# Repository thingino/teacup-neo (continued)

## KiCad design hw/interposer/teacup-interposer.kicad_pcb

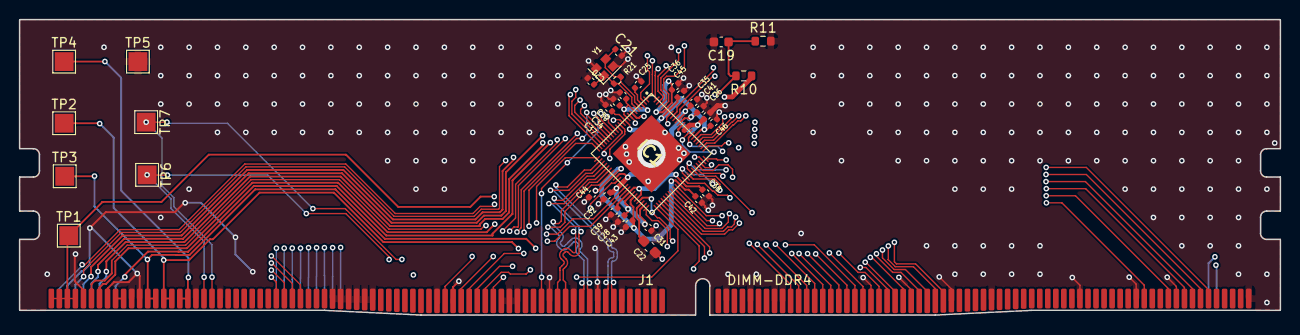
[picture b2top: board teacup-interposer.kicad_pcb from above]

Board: 4 copper layers, 133.3 x 31.2 mm, 35 parts (0 on the bottom side), 72 nets.

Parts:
C19: 100nF; C_0603_1608Metric
C20, C21: 12pF; C_0402_1005Metric
C22: 4.7uF; C_0603_1608Metric_Pad1.08x0.95mm_HandSolder
C25, C26, C28, C30, C31, C32, C34, C35, C36, C37, C38, C39, C41, C42, C43, C44, C45, C46: 100nF; C_0402_1005Metric
IC1: T31ZX; QFN35P900X900X90-89N-D
J1: DIMM-DDR4
R10, R11: 100k; R_0603_1608Metric
R21: 1M; R_0402_1005Metric
TP1: VCORE; TestPoint_Pad_2.0x2.0mm
TP2: +1V8; TestPoint_Pad_2.0x2.0mm
TP3: +3V3; TestPoint_Pad_2.0x2.0mm
TP4: +5V_SW; TestPoint_Pad_2.0x2.0mm
TP5: GND; TestPoint_Pad_2.0x2.0mm
TP6: USBA_HOST_DP; TestPoint_Pad_2.0x2.0mm
TP7: USBA_HOST_DM; TestPoint_Pad_2.0x2.0mm
Y1: 24 MHz; Crystal_SMD_2016-4Pin_2.0x1.6mm

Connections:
+1V8: C25.1, C26.1, C28.1, C30.1, C31.1, C32.1, C34.1, C35.1, IC1.3 (VDDIO_OSC), IC1.6 (PLL_VDDHV), IC1.9 (VDDIO0), IC1.31 (MIPI_AVD18), IC1.33 (ADC_VREF), IC1.34 (ADC_AVDD), IC1.38 (USB_AVD18), IC1.43 (CODEC_AVDD), IC1.75 (DDRVDD), IC1.76 (VDDMEM), IC1.79 (DDRPLL_VCCA), J1.15, J1.16, R10.1, TP2.1 (1_1)
+3V3: C36.1, C38.1, C39.1, IC1.37 (USB_AVD33), IC1.40 (VDDIO2), IC1.56 (VDDIO1_1), IC1.84 (VDDIO1_2), J1.13, J1.14, TP3.1 (1_1)
+5V_SW: J1.17, J1.18, TP4.1 (1_1)
/EXCLK_I: C20.1, IC1.5 (EXCLK_I), R21.1, Y1.1
/EXCLK_O: C21.1, IC1.4 (EXCLK_O), R21.2, Y1.3
/VCM: C22.1, IC1.42 (VCM)
/VREF: C19.1, IC1.77 (VREF), R10.2, R11.1
GMAC0_MDCK: IC1.58 (GMAC_MDCK_MSC1_D0_I2S_SDTO_SLCD_D4_PB10), J1.88
GMAC0_MDIO: IC1.57 (GMAC_MDIO_MSC1_D1_SLCD_D5_PB11), J1.87
GMAC0_PHYCLK: IC1.63 (GMAC_PHY_CLK_SLCD_D1_PB07), J1.90
GMAC0_RXD0: IC1.60 (GMAC_RXD0_I2S_DAC_LRCK_SLCD_WR_PB15/_SF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), J1.95
GMAC0_RXD1: IC1.61 (GMAC_RXD1_SLCD_TE_PB16/_SFC_GPC_PA25), J1.96
GMAC0_RXDV: IC1.59 (GMAC_RXDV_MSC1_CMD_I2S_SDTI_SLCD_D3_PB09), J1.94
GMAC0_TXCLK: IC1.62 (GMAC_TXCLK_SLCD_D0_PB06), J1.89
GMAC0_TXD0: IC1.64 (GMAC_TXD0_MSC1_D2_I2S_ADC_LRCK_SLCD_D6_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), J1.92
GMAC0_TXD1: IC1.65 (GMAC_TXD1_MSC1_D3_I2S_DAC_MCLK_SLCD_D7_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), J1.93
GMAC0_TXEN: IC1.66 (GMAC_TXEN_MSC1_CLK_I2S_ADC_MCLK_SLCD_D2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), J1.91
GND: C19.2, C20.2, C21.2, C22.2, C25.2, C26.2, C28.2, C30.2, C31.2, C32.2, C34.2, C35.2, C36.2, C37.2, C38.2, C39.2, C41.2, C42.2, C43.2, C44.2, C45.2, C46.2, IC1.89 (EP), J1.5, J1.8, J1.11, J1.12, J1.19, J1.22, J1.36, J1.37, J1.38, J1.39, J1.40, J1.41, J1.49, J1.51, J1.57, J1.58, J1.59, J1.63, J1.66, J1.69, J1.72, J1.76, J1.79, J1.82, J1.85, J1.86, J1.97, J1.102, J1.107, J1.112, J1.123, J1.130, J1.135, J1.144, J1.145, J1.147, J1.152, J1.169, J1.170, J1.171, J1.172, R11.2, TP5.1 (1_1), Y1.2 (G), Y1.4 (G)
GPIO0: IC1.80 (GPIO_PB31), J1.153
HPOUTL: IC1.44 (HPOUTL), J1.7
MICLP: IC1.41 (MICLP), J1.6
MIPI0_CLKN: IC1.26 (MIPI_CLKN_DVP_D3), J1.65
MIPI0_CLKP: IC1.27 (MIPI_CLKP_DVP_D2), J1.64
MIPI0_D0N: IC1.24 (MIPI_DATAN0_DVP_D5), J1.71
MIPI0_D0P: IC1.25 (MIPI_DATAP0_DVP_D4), J1.70
MIPI0_D1N: IC1.28 (MIPI_DATAN1_DVP_D1), J1.68
MIPI0_D1P: IC1.29 (MIPI_DATAP1_DVP_D0), J1.67
MIPI0_GPIO: IC1.16 (SA1_DVP_MCLK_PA15), J1.62
MSC0_CLK: IC1.51 (MSC0_CLK_SSI_SLV_CLK_PB04), J1.53
MSC0_CMD: IC1.52 (MSC0_CMD_SSI_SLV_CE0_PB05), J1.54
MSC0_D0: IC1.50 (MSC0_D0_SSI_SLV_DT_PB00), J1.52
MSC0_D1: IC1.49 (MSC0_D1_SSI_SLV_DR_PB01), J1.50
MSC0_D2: IC1.54 (MSC0_D2_PB02), J1.56
MSC0_D3_CD: IC1.53 (MSC0_D3_PB03), J1.55
MSC1_CLK: IC1.15 (CS2_DVP_HSYNC_SMB1_SDA_MSC1_CLK_PA16), J1.283
MSC1_CMD: IC1.14 (RD_DVP_VSYNC_SMB1_SCK_MSC1_CMD_PA17), J1.284
PWM0: IC1.1 (PWM0_SSI1_DT_PB17), J1.136
PWM1: IC1.2 (PWM1_SSI1_DR_PB18), J1.137
PWM2: IC1.86 (PWM2_SSI1_DT_DRV_VBUS_PB27), J1.138
PWM3: IC1.85 (PWM3_SSI1_DR_DMIC_CLK_PB28), J1.139
SAR_AUX0: IC1.32 (ADC_AUX0), J1.146
SFC_CLK: IC1.48 (SFC_CLK_PA27), J1.30
SFC_CS: IC1.45 (SFC_CE0_PA28), J1.32
SFC_IO0: IC1.47 (SFC_DT_PA23), J1.31
SFC_IO1: IC1.46 (SFC_DR_PA24), J1.29
SMB0_SCK: IC1.12 (SD7_SMB0_SCK_PA13), J1.149
SMB0_SDA: IC1.13 (SD6_SMB0_SDA_PA12), J1.148
SMB1_SCK: IC1.87 (SMB1_SCK_SSI1_CLK_PB26), J1.151
SMB1_SDA: IC1.88 (SMB1_SDA_SSI1_CE0_PB25), J1.150
SPARE_P173: IC1.7 (PPRST_), J1.173
SPARE_P174: IC1.8 (EFUSE_AVD), J1.174
SPARE_P175: IC1.11 (SA2_PA18), J1.175
SPARE_P176: IC1.17 (SA0_DVP_PCLK_PWM0_PA14), J1.176
SPARE_P177: IC1.22 (SD1_DVP_D7_UART1_RXD_PA07), J1.177
SPARE_P178: IC1.23 (SD0_DVP6_UART1_TXD_PA06), J1.178
SPARE_P179: IC1.67 (BOOT_SEL0_PC00), J1.179
SPARE_P180: IC1.73 (UART1_RXD_TMS_PB24), J1.180
SPARE_P181: IC1.74 (UART1_TXD_TCK_PB23), J1.181
SSI1_CE0: IC1.81 (SSI1_CE0_DMIC_DAT1_PB30), J1.134
SSI1_CLK: IC1.82 (SSI1_CLK_DMIC_DAT0_PB29), J1.131
UART0_CTS: IC1.69 (UART0_CTS_I2S_ADC_BCLK_SLCD_CS_PB20), J1.100
UART0_RTS: IC1.68 (UART0_RTS_I2S_DAC_BCLK_SLCD_DC_PB21), J1.101
UART0_RXD: IC1.71 (UART0_RXD_TDI_PB19), J1.98
UART0_TXD: IC1.70 (UART0_TXD_TDO_SLCD_RDY_PB22), J1.99
UART2_CTS: IC1.21 (SD2_DVP_D8_UART2_CTS_MSC1_D0_PA08), J1.105
UART2_RTS: IC1.20 (SD3_DVP_D9_UART2_RTS_MSC1_D1_PA09), J1.106
UART2_RXD: IC1.18 (SD5_DVP_D11_UART2_RXD_MSC1_D3_PA11), J1.103
UART2_TXD: IC1.19 (SD4_DVP_D10_UART2_TXD_MSC1_D2_PA10), J1.104
USBA_HOST_DM: IC1.35 (USB0PN), J1.21, TP7.1 (1_1)
USBA_HOST_DP: IC1.36 (USB0PP), J1.20, TP6.1 (1_1)
VCORE: C37.1, C41.1, C42.1, C43.1, C44.1, C45.1, C46.1, IC1.10 (VDD_1), IC1.30 (MIPI_AVD08), IC1.39 (VDD_2), IC1.55 (VDD_3), IC1.72 (VDD_4), IC1.78 (DDRPLL_VCCD), IC1.83 (VDD_5), J1.1, J1.2, J1.3, J1.4, TP1.1 (1_1)
VDDR: J1.9, J1.10

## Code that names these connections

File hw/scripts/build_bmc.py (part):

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    12: "BOOTSEL",
    13: "BMC_USB_DM", 14: "BMC_USB_DP",   # now via dedicated J9, not J2
    15: "RESET_EN",
    16: "SW5V_EN_ALT",               # GPIO select: alt-branch load switch (U14) -- native, margin testing
    17: "SFC_IO3", 18: "SFC_CS", 19: "SFC_IO0",
    20: "SFC_CLK", 21: "SFC_IO1", 22: "SFC_IO2",
    23: "HOSTED_SPI_MISO", 24: "HOSTED_SPI_CS",    # ESP-Hosted full-duplex SPI to interposer
    25: "HOSTED_HANDSHAKE",          # ESP-Hosted: co-processor -> host, data-ready-to-send
    26: "HOSTED_DATA_READY",         # ESP-Hosted: co-processor -> host, packet pending
    27: "U8_BOOT",                  # GPIO0/BOOT strap, R9 pull-up
    28: "EXP_INT",                   # U15 (TCA9555) interrupt, active low
    29: None, 35: None,              # spare
    30: "EN_CS_U4", 31: "EN_CS_U5",  # native, margin testing
    32: "USB_OC1", 33: "USB_OC2", 34: "USB_OC3",   # native -- fast overcurrent response
    36: "ESP32_CONSOLE_RX", 37: "ESP32_CONSOLE_TX",
    38: "SW5V_EN_BMC", 39: "VCORE_SNS",   # GPIO select: BMC-branch load switch (U4) -- native, margin testing
}
for num, spec in U8_PINS.items():
    ic_pin(U8, u8x, u8y, num, spec)
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    s.place(TS, ref, "TS5A3166", tx, y, 0, footprint="Package_TO_SOT_SMD:SOT-23-5",
            ref_at=(tx, y - S(6), 0), value_at=(tx, y + S(6), 0))
    ic_pin(TS, tx, y, 1, no_net)      # NO
    ic_pin(TS, tx, y, 2, "SFC_CS")    # COM
    ic_pin(TS, tx, y, 3, GNDF)        # GND
    ic_pin(TS, tx, y, 4, in_net)      # IN
    ic_pin(TS, tx, y, 5, P3V3F)       # V+
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s.place(SW, "SW1", "SSSS711403", swx, swy, 0,
        footprint="teacup-carrier:SW-TH_SSSS711403",
        ref_at=(swx, swy + S(4), 0), value_at=(swx, swy + S(6), 0))
ic_pin(SW, swx, swy, 1, "SW_SENSE_1")
ic_pin(SW, swx, swy, 3, GNDF)
ic_pin(SW, swx, swy, 4, "SW_SENSE_4")
# pins 2/5/6 deliberately NC per the confirmed datasheet pinout

vert2("Device:R", "R10", "10k", S(160), S(104), P3V3F, "SW_SENSE_1", "Resistor_SMD:R_0402_1005Metric")
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s.place(SW2, "SW2", "SSSS711403", sw2x, sw2y, 0,
        footprint="teacup-carrier:SW-TH_SSSS711403",
        ref_at=(sw2x, sw2y + S(4), 0), value_at=(sw2x, sw2y + S(6), 0))
ic_pin(SW2, sw2x, sw2y, 1, "EN_SW_BMC")
ic_pin(SW2, sw2x, sw2y, 3, "+5V_ALT")
ic_pin(SW2, sw2x, sw2y, 4, "EN_SW_ALT")
# pins 2/5/6 deliberately NC per the confirmed datasheet pinout

# ============ Primary NOR flash (U13, soldered SOIC-8 W25Q32JVSS) ============
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s.place(SOIC_NOR, "U13", "W25Q32JVSS", n4x, n4y, 0,
        footprint="Package_SO:SOIC-8_5.3x5.3mm_P1.27mm",
        ref_at=(n4x - S(10), n4y - S(10), 0), value_at=(n4x - S(10), n4y - S(8), 0))
ic_pin(SOIC_NOR, n4x, n4y, 1, "NOR_U4_CE")  # ~CS
ic_pin(SOIC_NOR, n4x, n4y, 2, "SFC_IO1")    # DO
ic_pin(SOIC_NOR, n4x, n4y, 3, "SFC_IO2")    # IO2
ic_pin(SOIC_NOR, n4x, n4y, 4, GNDF)         # GND (bottom)
ic_pin(SOIC_NOR, n4x, n4y, 5, "SFC_IO0")    # DI
ic_pin(SOIC_NOR, n4x, n4y, 6, "SFC_CLK")    # CLK
ic_pin(SOIC_NOR, n4x, n4y, 7, "SFC_IO3")    # IO3
ic_pin(SOIC_NOR, n4x, n4y, 8, P3V3F)        # VCC (top)
vert2("Device:C", "C24", "100nF", n4x + S(22), n4y, P3V3F, GNDF, "Capacitor_SMD:C_0402_1005Metric")

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s.place(DIP, "U11", "DIP-8 Socket", dx, dy, 0,
        footprint="Package_DIP:DIP-8_W7.62mm_Socket",
        ref_at=(dx - S(10), dy - S(10), 0), value_at=(dx - S(10), dy - S(8), 0))
ic_pin(DIP, dx, dy, 1, "NOR_U5_CE")   # ~CS
ic_pin(DIP, dx, dy, 2, "SFC_IO1")     # DO
ic_pin(DIP, dx, dy, 3, "SFC_IO2")     # IO2
ic_pin(DIP, dx, dy, 4, GNDF)          # GND (bottom)
ic_pin(DIP, dx, dy, 5, "SFC_IO0")     # DI
ic_pin(DIP, dx, dy, 6, "SFC_CLK")     # CLK
ic_pin(DIP, dx, dy, 7, "SFC_IO3")     # IO3
ic_pin(DIP, dx, dy, 8, P3V3F)         # VCC (top)
vert2("Device:C", "C25", "100nF", dx + S(22), dy, P3V3F, GNDF, "Capacitor_SMD:C_0402_1005Metric")

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    ic_pin(TPS, tx, ty, num, spec)

# ============ GPIO expander (U15, TCA9555PWR) ============
# Frees 9 native ESP32 GPIOs (USB_EN1-3, PG_SW5V/VCORE/SW5V_ALT, SW_SENSE_1/4,
# DCJACK_PRESENT) for the ESP-Hosted SPI link -- all slow status/enable
# signals with no real timing requirement, unlike flash chip-select and the
# power-domain switching GPIOs, which stay native for margin testing.
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s.place(EXP, "U15", "TCA9555PWR", ex, ey, 0,
        footprint="Package_SO:TSSOP-24_4.4x7.8mm_P0.65mm",
        ref_at=(ex - S(16), ey - S(24), 0), value_at=(ex - S(16), ey - S(22), 0))
ic_pin(EXP, ex, ey, 1, "EXP_INT")
ic_pin(EXP, ex, ey, 2, GNDF)     # A1
ic_pin(EXP, ex, ey, 3, GNDF)     # A2
ic_pin(EXP, ex, ey, 4, "USB_EN1")
ic_pin(EXP, ex, ey, 5, "USB_EN2")
ic_pin(EXP, ex, ey, 6, "USB_EN3")
ic_pin(EXP, ex, ey, 7, "PG_SW5V")
ic_pin(EXP, ex, ey, 8, "PG_VCORE")
ic_pin(EXP, ex, ey, 9, "PG_SW5V_ALT")
ic_pin(EXP, ex, ey, 10, "SW_SENSE_1")
ic_pin(EXP, ex, ey, 11, "SW_SENSE_4")
ic_pin(EXP, ex, ey, 12, GNDF)
ic_pin(EXP, ex, ey, 13, "DCJACK_PRESENT")
# pins 14-20 (P11-P17) deliberately NC -- spare I/O for future use
ic_pin(EXP, ex, ey, 21, GNDF)    # A0
ic_pin(EXP, ex, ey, 22, "I2C_PWR_SCL")
ic_pin(EXP, ex, ey, 23, "I2C_PWR_SDA")
ic_pin(EXP, ex, ey, 24, P3V3F)
vert2("Device:C", "C26", "100nF", ex, ey + S(35), P3V3F, GNDF, "Capacitor_SMD:C_0402_1005Metric")

# I2C_ID bus pull-ups (crosses J1 to whichever interposer's own EEPROM is
# seated, SS7 -- master on ESP32 GPIO6/7). Live on the carrier, not the
# interposer, because the carrier side is always populated regardless of
# which (or whether any) interposer is plugged in. 4.7k to +3V3.
vert2("Device:R", "R41", "4.7k", S(166), S(20), P3V3F, "I2C_ID_SDA", "Resistor_SMD:R_0402_1005Metric")
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
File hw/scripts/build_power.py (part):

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
s.flag("GND", P1(1), "P", "left")            # PGND
pin_net(P1(2), "+5V_SW", "left")             # VIN
pin_net(P1(3), "U1_EN", "left")              # EN
s.flag("GND", P1(4), "P", "left")            # MODE
s.flag("GND", P1(5), "P", "left")            # FSEL
pin_net(P1(6), "PG_VCORE", "left")           # PG (open-drain, R2 pulls up)
pin_net(P1(12), "VCORE_FB_SEL", "right")     # FB -- jumper common pole, see JP2-JP6 below
s.flag("GND", P1(11), "P", "right")          # GND
pin_net(P1(10), "U1_SS", "right")            # SS/TR
pin_net(P1(9), "U1_VCC", "right")            # VCC
pin_net(P1(8), "U1_SW", "right")             # SW
pin_net(P1(7), "U1_BST", "right")            # BST

# U1 passive islands
py1 = S(48)
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P2 = lambda n: s.pin(U2, u2x, u2y, 0, str(n))

s.flag("GND", P2(1), "P", "left")            # GND
pin_net(P2(2), "U2_SW", "left")              # SW
pin_net(P2(3), "+5V_SW", "left")             # VIN
pin_net(P2(4), "VDDR_FB_SEL", "right")       # FB -- jumper common pole, see JP7-JP10 below
pin_net(P2(5), "U2_EN", "right")             # EN
pin_net(P2(6), "U2_BST", "right")            # BST

py2 = S(84)
vert2("Device:C", "C6", "10uF", S(20), py2, "+5V_SW", GNDF, "Capacitor_SMD:C_0805_2012Metric")
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P7 = lambda n: s.pin(U2, u7x, u7y, 0, str(n))

s.flag("GND", P7(1), "P", "left")            # GND
pin_net(P7(2), "U7_SW", "left")              # SW
pin_net(P7(3), "+5V_SW", "left")             # VIN
pin_net(P7(4), "P3V3_FB", "right")           # FB
pin_net(P7(5), "U7_EN", "right")             # EN
pin_net(P7(6), "U7_BST", "right")            # BST

py7 = S(120)
vert2("Device:C", "C16", "10uF", S(20), py7, "+5V_SW", GNDF, "Capacitor_SMD:C_0805_2012Metric")
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s.place(DSCH, "D1", "PMEG2010ER", d1x, d1y, 0,
        footprint="Diode_SMD:Nexperia_CFP3_SOD-123W",
        ref_at=(d1x, d1y - S(3), 0), value_at=(d1x, d1y + S(3), 0))
pin_net(s.pin(DSCH, d1x, d1y, 0, "1"), "U5_VIN", "left")     # K
pin_net(s.pin(DSCH, d1x, d1y, 0, "2"), "+5V_BMC", "right")   # A

d2x, d2y = S(108), S(22)
s.place(DSCH, "D2", "PMEG2010ER", d2x, d2y, 0,
        footprint="Diode_SMD:Nexperia_CFP3_SOD-123W",
        ref_at=(d2x, d2y - S(3), 0), value_at=(d2x, d2y + S(3), 0))
pin_net(s.pin(DSCH, d2x, d2y, 0, "1"), "U5_VIN", "left")     # K
pin_net(s.pin(DSCH, d2x, d2y, 0, "2"), "+5V_ALT", "right")   # A

# ============ Always-on 3.3V LDO (U5, AZ1117CH-3.3) ============
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        footprint="Package_TO_SOT_SMD:SOT-223-3_TabPin2",
        extra_props={"Datasheet": "https://lcsc.com/product-detail/C92102.html"},
        ref_at=(u5x, u5y - S(6), 0), value_at=(u5x, u5y - S(4), 0))
pin_net(s.pin(REG, u5x, u5y, 0, "1"), "U5_VIN", "left")
s.flag("GND", s.pin(REG, u5x, u5y, 0, "2"), "P", "down")
pin_net(s.pin(REG, u5x, u5y, 0, "3"), "+3V3_ALWAYS", "right")
vert2("Device:C", "C14", "1uF", S(128), S(16), "U5_VIN", GNDF, "Capacitor_SMD:C_0603_1608Metric")
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# ============ BMC-branch load switch (U4, TPS22990DMLR) ============
# Gates +5V_BMC (the ESP32's own dedicated USB-C, isolated from every
# other source) onto the shared +5V_SW rail. EN_SW_BMC is arbitrated
# between GPIO (SW5V_EN_BMC, through R21), its own pulldown (R20), and
# SW2's throw1 on the bmc sheet (crosses in via this same label) -- one
# throw of the same on-off-on switch that forces the ALT branch (U14) on
# the other throw.
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        ref_at=(u4x, u4y - S(9), 0), value_at=(u4x, u4y + S(9), 0))
P4 = lambda n: s.pin(U4, u4x, u4y, 0, str(n))

pin_net(P4(1), "U4_CT", "left")              # CT
# pin 2 NC -- deliberately unconnected per datasheet
pin_net(P4(3), "+5V_BMC", "left")            # VIN
pin_net(P4(4), "+5V_BMC", "left")            # VBIAS (tied to VIN)
pin_net(P4(5), "EN_SW_BMC", "left")          # ON
s.flag("GND", P4(6), "P", "right")           # GND
pin_net(P4(7), "PG_SW5V", "right")           # PG (open-drain, R4 pulls up)
pin_net(P4(8), "+5V_SW", "right")            # VOUT
pin_net(P4(9), "+5V_SW", "right")            # VOUT
pin_net(P4(10), "+5V_SW", "right")           # VOUT
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# ============ ALT-branch load switch (U14, TPS22990DMLR) ============
# Gates +5V_ALT (the priority-OR'd DC jack / alt USB-C, see io.kicad_sch
# Q1/Q2) onto the same shared +5V_SW rail. EN_SW_ALT is arbitrated the
# same way as EN_SW_BMC (GPIO + pulldown) but is ALSO hard-overridable by
# SW2's throw4 on the bmc sheet, which ties this node to +5V_ALT (SW2's
# pole) when selected -- low-impedance, beats GPIO16's resistor-limited
# drive. Center = neither throw engaged, GPIO has full control.
U14 = "teacup-carrier:TPS22990DMLR"
u14x, u14y = S(210), S(76)
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        ref_at=(u14x, u14y - S(9), 0), value_at=(u14x, u14y + S(9), 0))
P14 = lambda n: s.pin(U14, u14x, u14y, 0, str(n))

pin_net(P14(1), "U14_CT", "left")            # CT
# pin 2 NC -- deliberately unconnected per datasheet
pin_net(P14(3), "+5V_ALT", "left")           # VIN
pin_net(P14(4), "+5V_ALT", "left")           # VBIAS (tied to VIN)
pin_net(P14(5), "EN_SW_ALT", "left")         # ON
s.flag("GND", P14(6), "P", "right")          # GND
pin_net(P14(7), "PG_SW5V_ALT", "right")      # PG (open-drain, R24 pulls up)
pin_net(P14(8), "+5V_SW", "right")           # VOUT (same shared rail as U4)
pin_net(P14(9), "+5V_SW", "right")           # VOUT
pin_net(P14(10), "+5V_SW", "right")          # VOUT
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vert2("Device:R", "R24", "10k", S(210), S(96), P3V3F, "PG_SW5V_ALT", "Resistor_SMD:R_0402_1005Metric")

# ALT-branch EN arbitration -- same topology as the BMC branch, plus SW2's
# hard override on the bmc sheet (crosses in via the EN_SW_ALT label).
vert2("Device:R", "R23", "1k", S(192), S(60), "SW5V_EN_ALT", "EN_SW_ALT", "Resistor_SMD:R_0402_1005Metric")
vert2("Device:R", "R22", "100k", S(201), S(60), "EN_SW_ALT", GNDF, "Resistor_SMD:R_0402_1005Metric")

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P3 = lambda n: s.pin(U3, u3x, u3y, 0, str(n))

s.flag("GND", P3(1), "P", "left")            # HVC/A0
pin_net(P3(2), "I2C_PWR_SCL", "left")        # SCL
pin_net(P3(3), "I2C_PWR_SDA", "left")        # SDA
s.flag("GND", P3(4), "P", "left")            # VSS
s.flag("GND", P3(5), "P", "left")            # P1B
pin_net(P3(6), "VDDR_FB_DIGIPOT", "left")    # P1W -- one jumper throw, not hard-wired to FB anymore
pin_net(P3(7), "VDDR", "left")               # P1A
pin_net(P3(8), "VCORE", "right")             # P0A
pin_net(P3(9), "VCORE_FB_DIGIPOT", "right")  # P0W -- one jumper throw, not hard-wired to FB anymore
s.flag("GND", P3(10), "P", "right")          # P0B
s.flag("+3V3", P3(11), "P", "right")         # WP
s.flag("GND", P3(12), "P", "right")          # A2
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vert2("Device:C", "C12", "100nF", S(200), S(130), P3V3F, GNDF, "Capacitor_SMD:C_0402_1005Metric")

# I2C_PWR bus pull-ups (digipot U3 + GPIO expander U15 on the bmc sheet,
# master on ESP32 GPIO4/5) -- neither device supplies its own, and I2C is
# open-drain, so without these the bus simply doesn't work. 4.7k to +3V3,
# standard value for a short, low-device-count, carrier-local bus.
vert2("Device:R", "R25", "4.7k", S(209), S(130), P3V3F, "I2C_PWR_SDA", "Resistor_SMD:R_0402_1005Metric")
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# ============ VCORE/VDDR voltage-select jumpers ============
# Explicit user direction: replace "trust the digipot's NV memory" as the
# power-up safety story with a hardware-deterministic default. U1/U2's FB
# pins (VCORE_FB_SEL / VDDR_FB_SEL above) are now the common pole of a
# jumper bank, not hard-wired to the digipot wiper. Every candidate divider
# -- 4 fixed presets for VCORE, 3 for VDDR, plus the digipot itself as one
# more candidate -- stays permanently powered across VOUT/GND regardless of
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def jumper(ref, val, x, y, pole_net, throw_net):
    # Ref/value pushed above/below the pin span (matching the headers
    # sheet's proven convention) rather than vert2's default beside-the-body
    # offset -- the pole/throw net labels here (VCORE_FB_SEL etc.) are long
    # enough to run into a close-beside ref/value at this tight jumper
    # pitch. Confirmed via check_overlaps.py.
    s.place(JHDR, ref, val, x, y, 0, footprint=JFP,
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
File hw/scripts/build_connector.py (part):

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    49: "GND", 50: "MSC0_D1", 51: "GND",
    52: "MSC0_D0", 53: "MSC0_CLK", 54: "MSC0_CMD", 55: "MSC0_D3_CD", 56: "MSC0_D2",
    57: "GND",
    # Headphone/mic (HPOUTL/MICLP) don't live here -- moved to unit 1 pins
    # 6/7 as of 2026-07-15 (previously unit 4's 170/171, and before that
    # this same pin 58). 58 folds into the existing GND bracket either side
    # of it (57/59), same analog-isolation intent, now a solid block.
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    # 60-62 rotated left by one (SDA/SCL/GPIO instead of GPIO/SDA/SCL),
    # matching MIPI1's same rotation, per explicit user direction,
    # 2026-07-15.
    60: "MIPI0_SCCB_SDA", 61: "MIPI0_SCCB_SCL", 62: "MIPI0_GPIO",
    63: "GND", 64: "MIPI0_CLKP", 65: "MIPI0_CLKN",
    66: "GND", 67: "MIPI0_D1P", 68: "MIPI0_D1N",
    69: "GND", 70: "MIPI0_D0P", 71: "MIPI0_D0N",
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    # MIPI1: same pattern, same reasoning (matches J8's FFC pin order).
    # 73-75 rotated left by one (SDA/SCL/GPIO instead of GPIO/SDA/SCL) per
    # explicit user direction, 2026-07-15.
    73: "MIPI1_SCCB_SDA", 74: "MIPI1_SCCB_SCL", 75: "MIPI1_GPIO",
    76: "GND", 77: "MIPI1_CLKP", 78: "MIPI1_CLKN",
    79: "GND", 80: "MIPI1_D1P", 81: "MIPI1_D1N",
    82: "GND", 83: "MIPI1_D0P", 84: "MIPI1_D0N",
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    unit_pin(u3x, u3y, 3, num, spec)

# ============ Unit 4 (pins 145-192): SAR-ADC + general SMB/I2C + plain GPIO ============
# SAR_AUX0 matches the T41 reference board's dedicated ADC_AUX0 pin (old/docs/
# t31zx_teacup_pinuse.csv pin 32) -- a single-channel analog input outside the
# GPIO mux tables on every SoC checked, not a multi-channel SADC. SMB0/SMB1 here
# are the carrier's GENERAL system I2C headers -- kept electrically separate
# from I2C_ID_SDA/SCL (unit 1, pins 23/24, the carrier-ID EEPROM bus), same
# isolation principle already used for VGA/HDMI DDC on the A1 interposer (SS10).
# GPIO0-15 are plain unclaimed superset pins for whatever's left after every
# named peripheral above -- deliberately generic, not tied to a specific SoC
# pin identity, since "remaining plain GPIO" is itself one of the user's
# approved header clusters. Pins 170-192 (23 pins), plus all of units 5-6
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for i in range(16):
    UNIT4[153 + i] = f"GPIO{i}"
UNIT4[169] = "GND"
# HPOUTL/MICLP moved from here (170/171) to unit 1 pins 6/7 -- per explicit
# user direction, 2026-07-15. 170/171 revert to GND (matching 169/172, so
# this whole run is now a solid GND block rather than leaving a gap).
UNIT4[170] = "GND"
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
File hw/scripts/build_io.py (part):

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s.place(AO3401A, "Q1", "AO3401A", q1x, q1y, 0,
        footprint="Package_TO_SOT_SMD:SOT-23",
        ref_at=(q1x - S(8), q1y - S(3), 0), value_at=(q1x - S(8), q1y + S(3), 0))
q_pin(AO3401A, q1x, q1y, AO_S, "DCJACK_VBUS")
q_pin(AO3401A, q1x, q1y, AO_D, "+5V_ALT")
q_pin(AO3401A, q1x, q1y, AO_G, "Q1_GATE")
vert2("Device:R", "R15", "100k", q1x, S(145), "Q1_GATE", GNDF, "Resistor_SMD:R_0402_1005Metric")

q2x, q2y = S(105), S(130)
s.place(AO3401A, "Q2", "AO3401A", q2x, q2y, 0,
        footprint="Package_TO_SOT_SMD:SOT-23",
        ref_at=(q2x - S(8), q2y - S(3), 0), value_at=(q2x - S(8), q2y + S(3), 0))
q_pin(AO3401A, q2x, q2y, AO_S, "ALTUSB_VBUS")
q_pin(AO3401A, q2x, q2y, AO_D, "+5V_ALT")
q_pin(AO3401A, q2x, q2y, AO_G, "Q2_GATE")
vert2("Device:R", "R16", "4.7k", S(105), S(145), "DCJACK_VBUS", "Q2_GATE", "Resistor_SMD:R_0402_1005Metric")
vert2("Device:R", "R17", "100k", S(114), S(145), "Q2_GATE", GNDF, "Resistor_SMD:R_0402_1005Metric")
# Bulk/bypass cap at the OR'd output node, before +5V_ALT reaches U14
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})

# ============ External amplifier/mic tap (J38) ============
# 3-pin header (HPOUTL, GND, MICLP) tapping the same three audio signals
# J6 carries, in parallel with the jack itself, so an external amplifier
# AND an external mic can both be wired in directly instead of needing a
# breakout cable off J6. GND placed in the middle (rather than at the
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
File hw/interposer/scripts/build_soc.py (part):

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    "11": ("NET", "SPARE_P175"),
    "12": ("NET", "SMB0_SCK"), "13": ("NET", "SMB0_SDA"),
    "14": ("NET", "MSC1_CMD"), "15": ("NET", "MSC1_CLK"),
    "16": ("NET", "MIPI0_GPIO"),
    "17": ("NET", "SPARE_P176"),
    "18": ("NET", "UART2_RXD"), "19": ("NET", "UART2_TXD"),
    "20": ("NET", "UART2_RTS"), "21": ("NET", "UART2_CTS"),
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    "75": ("RAIL", "+1V8"), "76": ("RAIL", "+1V8"),
    "77": ("LOCAL", "VREF"),
    "78": ("RAIL", "VCORE"), "79": ("RAIL", "+1V8"),
    "80": ("NET", "GPIO0"),
    "81": ("NET", "SSI1_CE0"), "82": ("NET", "SSI1_CLK"),
    "83": ("RAIL", "VCORE"), "84": ("RAIL", "+3V3"),
    "85": ("NET", "PWM3"), "86": ("NET", "PWM2"),
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            s.label(spec, p[0], p[1], LABEL_ANGLE[d], global_=spec in RAIL_NAMES)

# --- Crystal: Y1 (24MHz) + C20/C21 (12pF load) + R21 (1M feedback) ---
# Y1 pin1->EXCLK_I, pin3->EXCLK_O, pin2 (case, shared position with hidden
# pin4)->GND -- exact TeaCup 3.3 topology, using Crystal_GND24 since the
# real part is a 4-pad case-grounded crystal, not a plain 2-pin one.
CRYSTAL = "Device:Crystal_GND24"
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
